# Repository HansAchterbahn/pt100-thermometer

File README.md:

# pt100-thermometer
_Entwicklungsdaten für ein einfaches elektronisches Thermometer_  

Die Entwicklungsdaten in diesem Repro werden auf meinem Blog https://aetzenloetenprogrammieren.blogspot.com genauer beschrieben.  

## Messprinzip

## Foto der fertigen Platine

## Schaltplan

## Boardlayout

## Verzeichnisstruktur

* Datenblätter  
 -- AD620.pdf  
 -- TS914.pdf  
* Layout  
 * Eagle  
  -- PT100-SensorPCB008.brd  
  -- PT100-SensorPCB008.sch  
  -- PT100-SensorPCB008-Board.pdf  
  -- PT100-SensorPCB008-Schaltplan.pdf  
 * Fritzing(Breadboard)  
   -- Thermometer-PT100-fritzing.fzz  
   -- Thermometer-PT100-fritzing.png  
* Simulation  
 * LTSpice  
   -- Thermometer-PT100-LTSpice.asc  
   -- Thermometer-PT100-LTSpice.png  
 * Mathematica  
   -- PT100Kennlinie.cdf  
   -- PT100Kennlinie.png  

## Verwendete Programme

__Schaltplan, Leiterplattenlayout und Breadbord:__

Eagle - Erstellen von Schaltplan und Leiterplattenlayout  
http://www.autodesk.com/products/eagle/overview  

Fritzing - Erstellen des Breadbords  
http://fritzing.org/home/  

__Simulation__

LTSpice - Simulation des Schaltplans  
http://www.linear.com/designtools/software/#LTspice  

Mathematica - Animation der Temperaturkennlinie (Kann mit dem kostenlosen Wolfram CDF Player abgespielt werden)  
http://www.wolfram.com/mathematica/  
https://www.wolfram.com/cdf-player/

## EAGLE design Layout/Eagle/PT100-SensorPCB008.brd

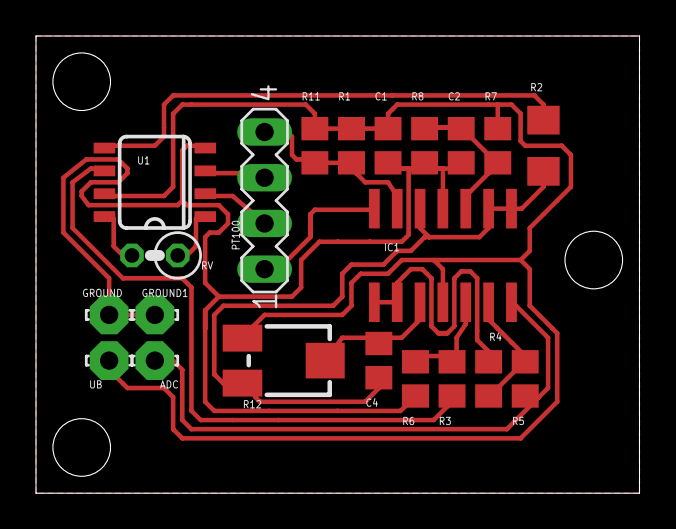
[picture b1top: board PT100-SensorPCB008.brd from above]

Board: 2 copper layers, 33.5 x 25.4 mm, 21 parts (0 on the bottom side), 17 nets.

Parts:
ADC: LSP10
C1, C2, C4: 100n; C0805
GROUND, GROUND1: LSP10
IC1: TS914; SO14
PT100: MA04-1
R1: 3k; R0805
R2: 0; R1206
R3, R4: 1,8k; R0805
R5, R6, R7, R8, R11: 15k; R0805
R12: 5k; RTRIM3374
RV: 5,49k; 0207/2V
U1: AD620; SO08-TIGHT
UB: LSP10

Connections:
+3V3: C1.1, IC1.4, R1.2, R7.1, R11.2, R12.1, U1.7, UB.MP
GND: C1.2, C2.2, GROUND.MP, GROUND1.MP, IC1.11, R6.2, R8.2, U1.4
INST_A: R3.2, U1.6
INST_E-NEG: IC1.13, PT100.4, R1.1, R11.1
INST_E-POS: PT100.2, U1.2
unnamed: RV.2, U1.8
unnamed: RV.1, U1.1
unnamed: IC1.14, PT100.1
unnamed: R2.1, U1.5
unnamed: PT100.3, U1.3
unnamed: C4.1, IC1.3, R12.2
unnamed: IC1.6, R4.1, R5.2
unnamed: IC1.5, R3.1, R6.1
unnamed: ADC.MP, IC1.7, R5.1
unnamed: C2.1, IC1.10, R7.2, R8.1
SYMGND: C4.2, IC1.8, IC1.9, IC1.12, R2.2, R12.3
UREF: IC1.1, IC1.2, R4.2

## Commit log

2017-01-15 Eagledaten hinzugefügt Datenblätter hinzugefügt
2017-01-27 Mathematica CDF Kennlinie hinzugefügt
2017-01-29 Verzeichnisstruktur geändert Simulationsdaten hinzugefügt • Mathematica • LTSpice README Erweitert
2017-01-29 Änderungen an README

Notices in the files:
parts and their libraries:
SparkFun-AnalogIC: Licensing:Creative Commons ShareAlike 4.0 International - https://creativecommons.org/licenses/by-sa/4.0
